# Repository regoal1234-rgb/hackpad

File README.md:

# Junsuh's macropad
Hello! This is my submission for hackpad! This was made for Hackpad v1.

## Features
- A big 0.96" OLED screen
- 15x whole cherry keys 
- kmk firmware! Control your mouse with this macropad

## PCB
Here are pictures of my pcb:

| **Schematic** | **PCB** |
|---------------|---------|
||
|

[x] I ran DRC and there are 0 errors

## CAD
Designed using Autodesk Fusion! It was painful. Be glad you have the current guide, I spent 10+ hours figuring out how to do everything correctly (and even like this I still did stupid stuff).

Everything fits together with 4 m3 screws and bolts

## Firmware

I wrote the firmware using kmk, you can see it inside the repo. It can be used to control your mouse!

## Notes
Making the pad was fun enthough i went through hardships. Ended up learning how to use OpenSCAD and FreeCAD.

## BOM
- 1 Seeed XIAO RP2040
- 15x [MX-Style switches]
- 15x Through-hole 1N4148 Diodes
- 1x 0.91 inch OLED displays (5V VCC, 3.3V logic, I2C)
- 1x 3D PRINTED CASE
- 15x Blank DSA keycaps
- 1x EC11 Rotary encoders
- 4x M3x16mm screws
- 4x M3x5mx4mm heatset inserts

CAD Source

The CAD source file for this project is included below.

Fusion 360 file (.f3d): https://github.com/regoal1234-rgb/hackpad/blob/main/CAD/final.f3z

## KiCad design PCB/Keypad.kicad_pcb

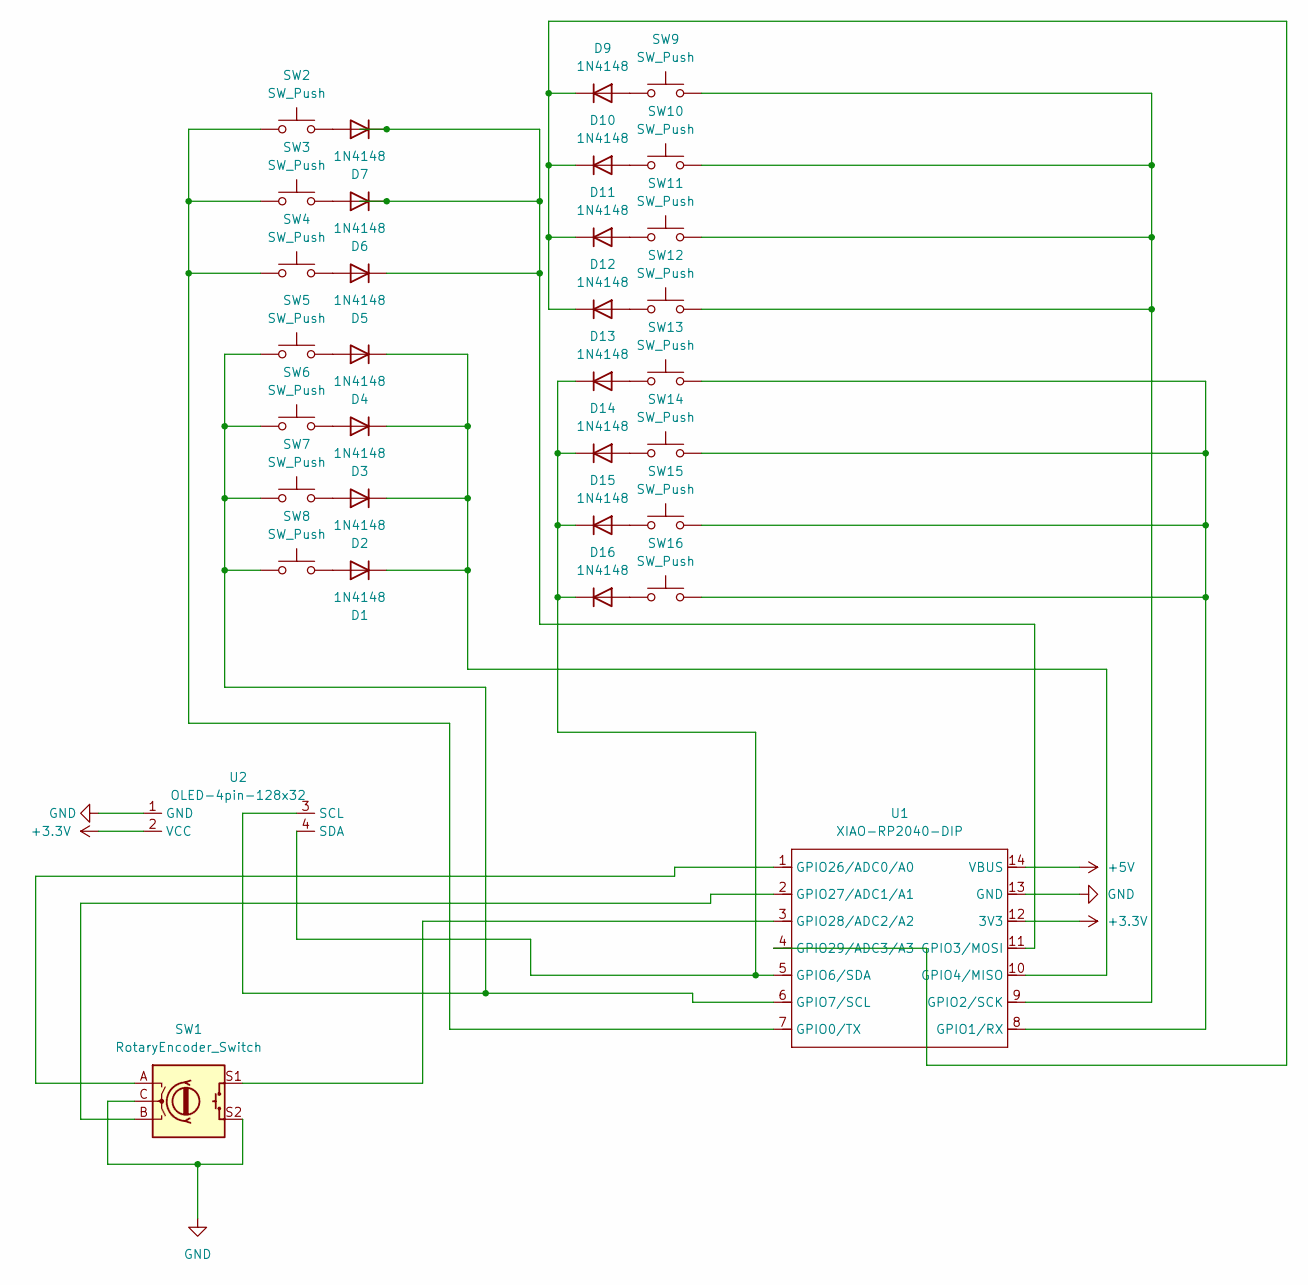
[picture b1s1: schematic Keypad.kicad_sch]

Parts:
D1, D2, D3, D4, D5, D6, D7, D9, D10, D11, D12, D13, D14, D15, D16: 1N4148; D_DO-35_SOD27_P7.62mm_Horizontal
SW1: RotaryEncoder_Switch; RotaryEncoder_Alps_EC11E-Switch_Vertical_H20mm_CircularMoun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
SW2, SW3, SW4, SW5, SW6, SW7, SW8, SW9, SW10, SW11, SW12, SW13, SW14, SW15, SW16: SW_Push; SW_Cherry_MX_1.00u_PCB
U1: XIAO-RP2040-DIP
U2: OLED-4pin-128x32; SSD1306-0.91-OLED-4pin-128x32

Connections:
+3.3V: U1.12 (3V3), U2.2 (VCC)
+5V: U1.14 (VBUS)
GND: SW1.C, SW1.S2, U1.13 (GND), U2.1 (GND)
unnamed: D1.2 (A), SW8.2
unnamed: D1.1 (K), D2.1 (K), D3.1 (K), D4.1 (K), U1.10 (GPIO4/MISO)
unnamed: D2.2 (A), SW7.2
unnamed: D3.2 (A), SW6.2
unnamed: D4.2 (A), SW5.2
unnamed: D5.2 (A), SW4.2
unnamed: D5.1 (K), D6.1 (K), D7.1 (K), U1.11 (GPIO3/MOSI)
unnamed: D6.2 (A), SW3.2
unnamed: D7.2 (A), SW2.2
unnamed: D9.2 (A), SW9.1
unnamed: D10.2 (A), SW10.1
unnamed: D9.1 (K), D10.1 (K), D11.1 (K), D12.1 (K), U1.4 (GPIO29/ADC3/A3)
unnamed: D11.2 (A), SW11.1
unnamed: D12.2 (A), SW12.1
unnamed: D13.2 (A), SW13.1
unnamed: D13.1 (K), D14.1 (K), D15.1 (K), D16.1 (K), U1.5 (GPIO6/SDA), U2.4 (SDA)
unnamed: D14.2 (A), SW14.1
unnamed: D15.2 (A), SW15.1
unnamed: D16.2 (A), SW16.1
unnamed: SW2.1, SW3.1, SW4.1, U1.7 (GPIO0/TX)
unnamed: SW13.2, SW14.2, SW15.2, SW16.2, U1.8 (GPIO1/RX)
unnamed: SW9.2, SW10.2, SW11.2, SW12.2, U1.9 (GPIO2/SCK)
unnamed: SW5.1, SW6.1, SW7.1, SW8.1, U1.6 (GPIO7/SCL), U2.3 (SCL)
unnamed: SW1.A, U1.1 (GPIO26/ADC0/A0)
unnamed: SW1.B, U1.2 (GPIO27/ADC1/A1)
unnamed: SW1.S1, U1.3 (GPIO28/ADC2/A2)

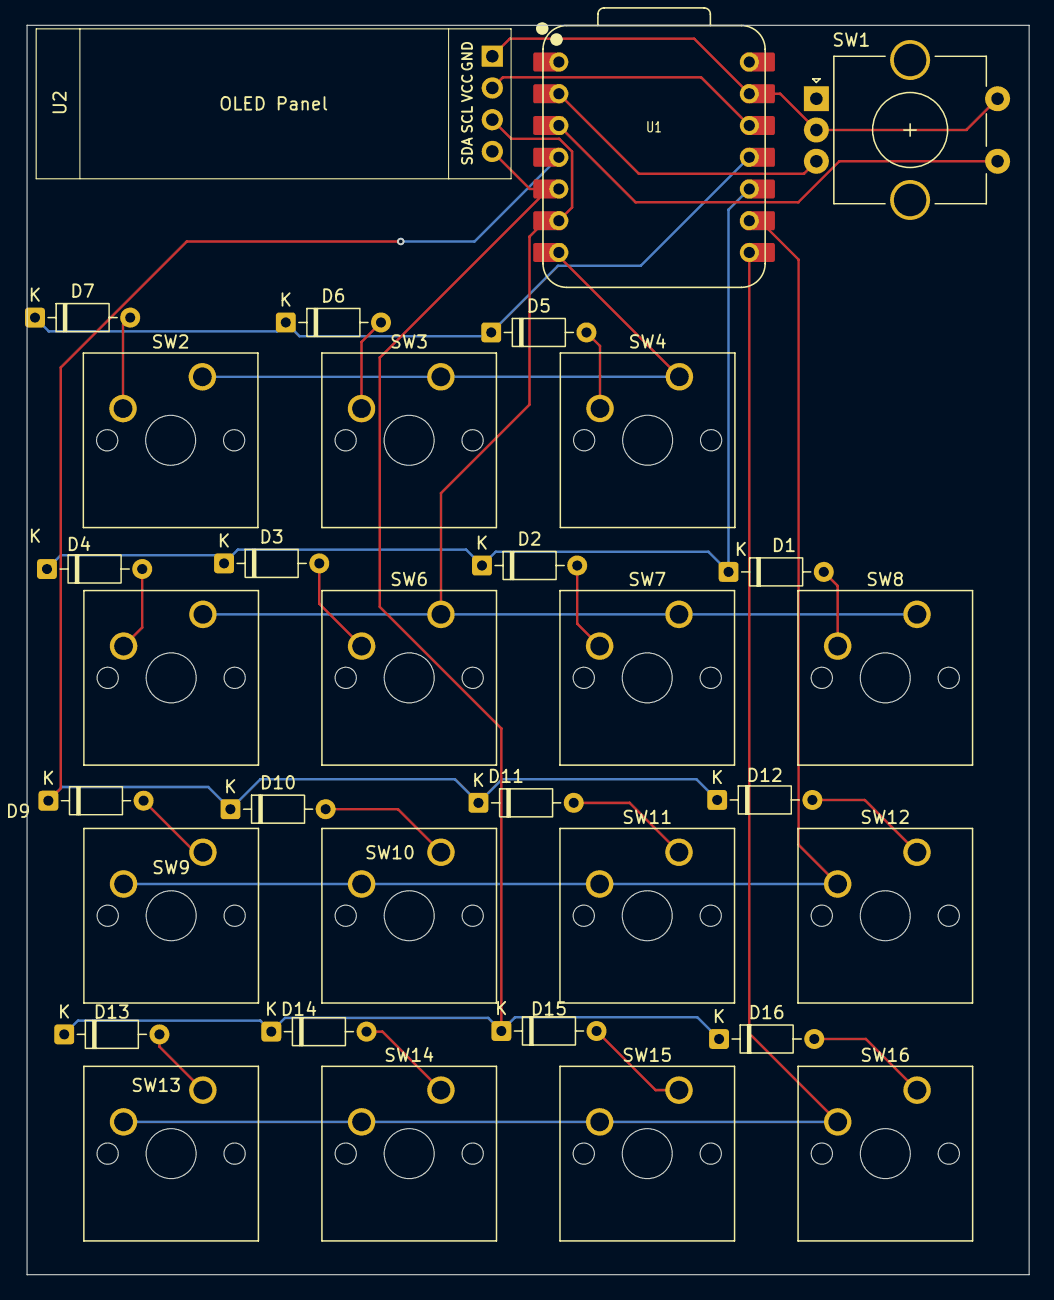
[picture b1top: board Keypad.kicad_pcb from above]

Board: 2 copper layers, 80.2 x 100.0 mm, 33 parts (0 on the bottom side), 28 nets.

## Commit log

2025-12-18 Add README
2026-02-08 cad files
2026-02-14 README.md
2026-02-27 Rename Keypad (2).step to Keypad.step
